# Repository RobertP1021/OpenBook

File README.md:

# OpenBook

## Diagrama

## Bill Of Materials

| Componenta | Datasheet | Model |
|------------|-----------|-------|
| ESP32-C6-WROOM-1-N8 | [Datasheet](https://www.espressif.com/sites/default/files/documentation/esp32-c6_datasheet_en.pdf) | [Model](https://www.snapeda.com/parts/ESP32-C6-WROOM-1-N8/Espressif+Systems/view-part/?ref=eda) |
| W25Q512JVEIQ | [Datasheet](https://www.winbond.com/resource-files/W25Q512JV%20RevI%2005132020%20Plus.pdf) | [Model](https://www.snapeda.com/parts/W25Q512JVEIQ/Winbond+Electronics/view-part/?ref=eda) |
| DS3231SN# | [Datasheet](https://datasheets.maximintegrated.com/en/ds/DS3231.pdf) | [Model](https://www.snapeda.com/parts/DS3231SN%23/Analog+Devices/view-part/?ref=eda) |
| MAX17048G+T10 | [Datasheet](https://datasheets.maximintegrated.com/en/ds/MAX17048-MAX17049.pdf) | [Model](https://www.snapeda.com/parts/MAX17048G+T10/Analog+Devices/view-part/?ref=eda) |
| BME688 | [Datasheet](https://www.bosch-sensortec.com/media/boschsensortec/downloads/datasheets/bst-bme688-ds000.pdf) | [Model](https://www.snapeda.com/parts/BME680/Bosch/view-part/?welcome=home) |
| MCP73831 | [Datasheet](https://ww1.microchip.com/downloads/en/DeviceDoc/20001984g.pdf) | [Model](https://www.snapeda.com/parts/MCP73831T-2ACI-OT/Microchip/view-part/?ref=eda) |
| BD5229G-TR | [Datasheet](https://fscdn.rohm.com/en/products/databook/datasheet/ic/power/voltage_detector/bd52xxg-e.pdf) | [Model](https://componentsearchengine.com/part-view/BD5229G-TR/ROHM%20Semiconductor) |
| USBLC6-2SC6Y | [Datasheet](https://www.st.com/resource/en/datasheet/usblc6-2.pdf) | [Model](https://www.snapeda.com/parts/USBLC6-2SC6Y/STMicroelectronics/view-part/?ref=eda) |
| 112A-TAAR-R03 | [Datasheet](https://www.attend.com.tw/sites/default/files/2022-05/112A-TAAR-R03.pdf) | [Model](https://www.snapeda.com/parts/112A-TAAR-R03/ATTEND/view-part/?ref=eda) |
| FH34SRJ-24S-0.5SH | [Datasheet](https://www.hirose.com/product/document?clcode=CL0684-0832-7-99&productname=FH34SRJ-24S-0.5SH(99)&series=FH34&documenttype=Catalog&lang=en&documentid=D49681_en) | [Model](https://www.snapeda.com/parts/FH34SRJ-24S-0.5SH(99)/Hirose/view-part/?ref=eda) |
| DMG2305UX-7 | [Datasheet](https://www.diodes.com/assets/Datasheets/DMG2305UX.pdf) | [Model](https://www.snapeda.com/parts/DMG2305UX-7/Diodes%20Inc./view-part/?ref=eda) |
| SI1308EDL-T1-GE3 | [Datasheet](https://www.vishay.com/docs/68732/si1308edl.pdf) | [Model](https://www.snapeda.com/parts/SI1308EDL-T1-GE3/Vishay+Siliconix/view-part/?ref=snap) |
| MBR0530 | [Datasheet](https://www.onsemi.com/pdf/datasheet/mbr0520lt1-d.pdf) | [Model](https://www.snapeda.com/parts/MBR0530/Onsemi/view-part/?ref=eda) |
| PGB1010603MR | [Datasheet](https://www.littelfuse.com/media?resourcetype=datasheets&itemid=3d1e98b7-4d37-463c-9380-c56c83b11c3c&filename=littelfuse-pulseguard-pgb1) | [Model](https://www.snapeda.com/parts/PGB1010603MR/Littelfuse/view-part/?ref=eda) |
| XC6220A331MR-G | [Datasheet](https://www.torexsemi.com/file/xc6220/XC6220.pdf) | [Model](https://www.snapeda.com/parts/XC6220A331MR-G/Torex+Semiconductor/view-part/?ref=eda) |
| EVQPUJ02K | [Datasheet](https://industrial.panasonic.com/cdbs/www-data/pdf/ATV0000/ATV0000CE5.pdf) | [Model](https://www.snapeda.com/parts/EVQPUJ02K/Panasonic/view-part/?ref=eda) |
| GDEH0154D67 | [Datasheet](https://www.good-display.com/companyfile/203.html) | [Model](https://www.good-display.com/product/207.html) |
| CPH3225A | [Datasheet](https://www.sii.co.jp/en/quartz/files/2021/03/CPH3225A_E.pdf) | [Model](https://www.snapeda.com/parts/CPH3225A/Seiko+Instruments/view-part/?ref=eda) |

## Functionalitatea hardware

Proiectul foloseste un ESP32-C6 ca microcontroller central, cu urmatoarele componente principale:

1. **Display E-Ink (GDEH0154D67)** - afisaj de 1.54" cu 200x200 pixeli conectat prin SPI, perfect pentru afisarea datelor cu consum minim de energie, deoarece consuma curent doar la actualizarea ecranului.

2. **Memorie Flash externa (W25Q512JVEIQ)** - 64MB de stocare SPI pentru date, configuratii si loguri cand dispozitivul este in modul deep sleep.

3. **Senzor de mediu (BME688)** - masoara temperatura, umiditatea, presiunea atmosferica si calitatea aerului, conectat prin I2C.

4. **Ceas RTC (DS3231)** - mentine ora exacta chiar si cand dispozitivul este oprit, conectat prin I2C.

5. **Sistem de alimentare**: 
   - Baterie LiPo 3.7V
   - Circuit de incarcare (MCP73831)
   - Monitor baterie (MAX17048G)
   - Regulator LDO 3.3V (XC6220A331MR-G)
   - Convertor 5V (pentru componente care necesita 5V)

6. **Interfata USB-C** - pentru incarcare si comunicatii, cu protectie ESD (USBLC6-2SC6Y).

7. **Butoane tactile (EVQPUJ02K)** - 3 butoane pentru interfata utilizator.

8. **Slot card microSD** - pentru stocarea datelor in volum mare.

## Descrierea pinilor ESP32-C6

- **GPIO1-2**: Magistrala I2C principala pentru conectarea senzorilor si RTC-ului DS3231, fiind pinii hardware dedicati pentru I2C.

- **GPIO3**: Pin RESET pentru reinitializarea sistemului.

- **GPIO4**: SS_SD pentru selectarea cardului microSD, parte a interfetei SPI dedicate cardului.

- **GPIO5**: Pin EPD_DC pentru controlul displayului E-Ink (Data/Command).

- **GPIO6**: Pin SPI SCK (clock) utilizat pentru comunicatia cu displayul si alte dispozitive SPI.

- **GPIO7**: Pin MOSI pentru transferul de date spre dispozitivele SPI.

- **GPIO8-9**: Pini pentru interfata RTC (32kHz si INT_RTC), utilizati pentru wake-up si sincronizare.

- **GPIO10**: Pin pentru controlul FLASH_CS, selectand memoria flash externa.

- **GPIO11**: Pin EPD_CS pentru selectarea displayului E-Ink.

- **GPIO12**: Pin EPD_RST pentru resetarea displayului E-Ink.

- **GPIO13-14**: Pini USB_D- si USB_D+ pentru comunicatia USB.

- **GPIO15**: Pin IO/BOOT pentru controlul bootarii sistemului.

- **GPIO16-18**: Pini pentru controlul displayului e-ink (EPD_3V3, EPD_BUSY).

- **GPIO19-21**: Pini SCL, SDA pentru o secunda interfata I2C folosita pentru comunicatie cu senzorii adaugati.

- **GPIO22-23**: Pini pentru control I/O general si semnale de control pentru display.

- **GPIO26-28**: Pini pentru LED-uri de status si controlul modulului.

## Poze

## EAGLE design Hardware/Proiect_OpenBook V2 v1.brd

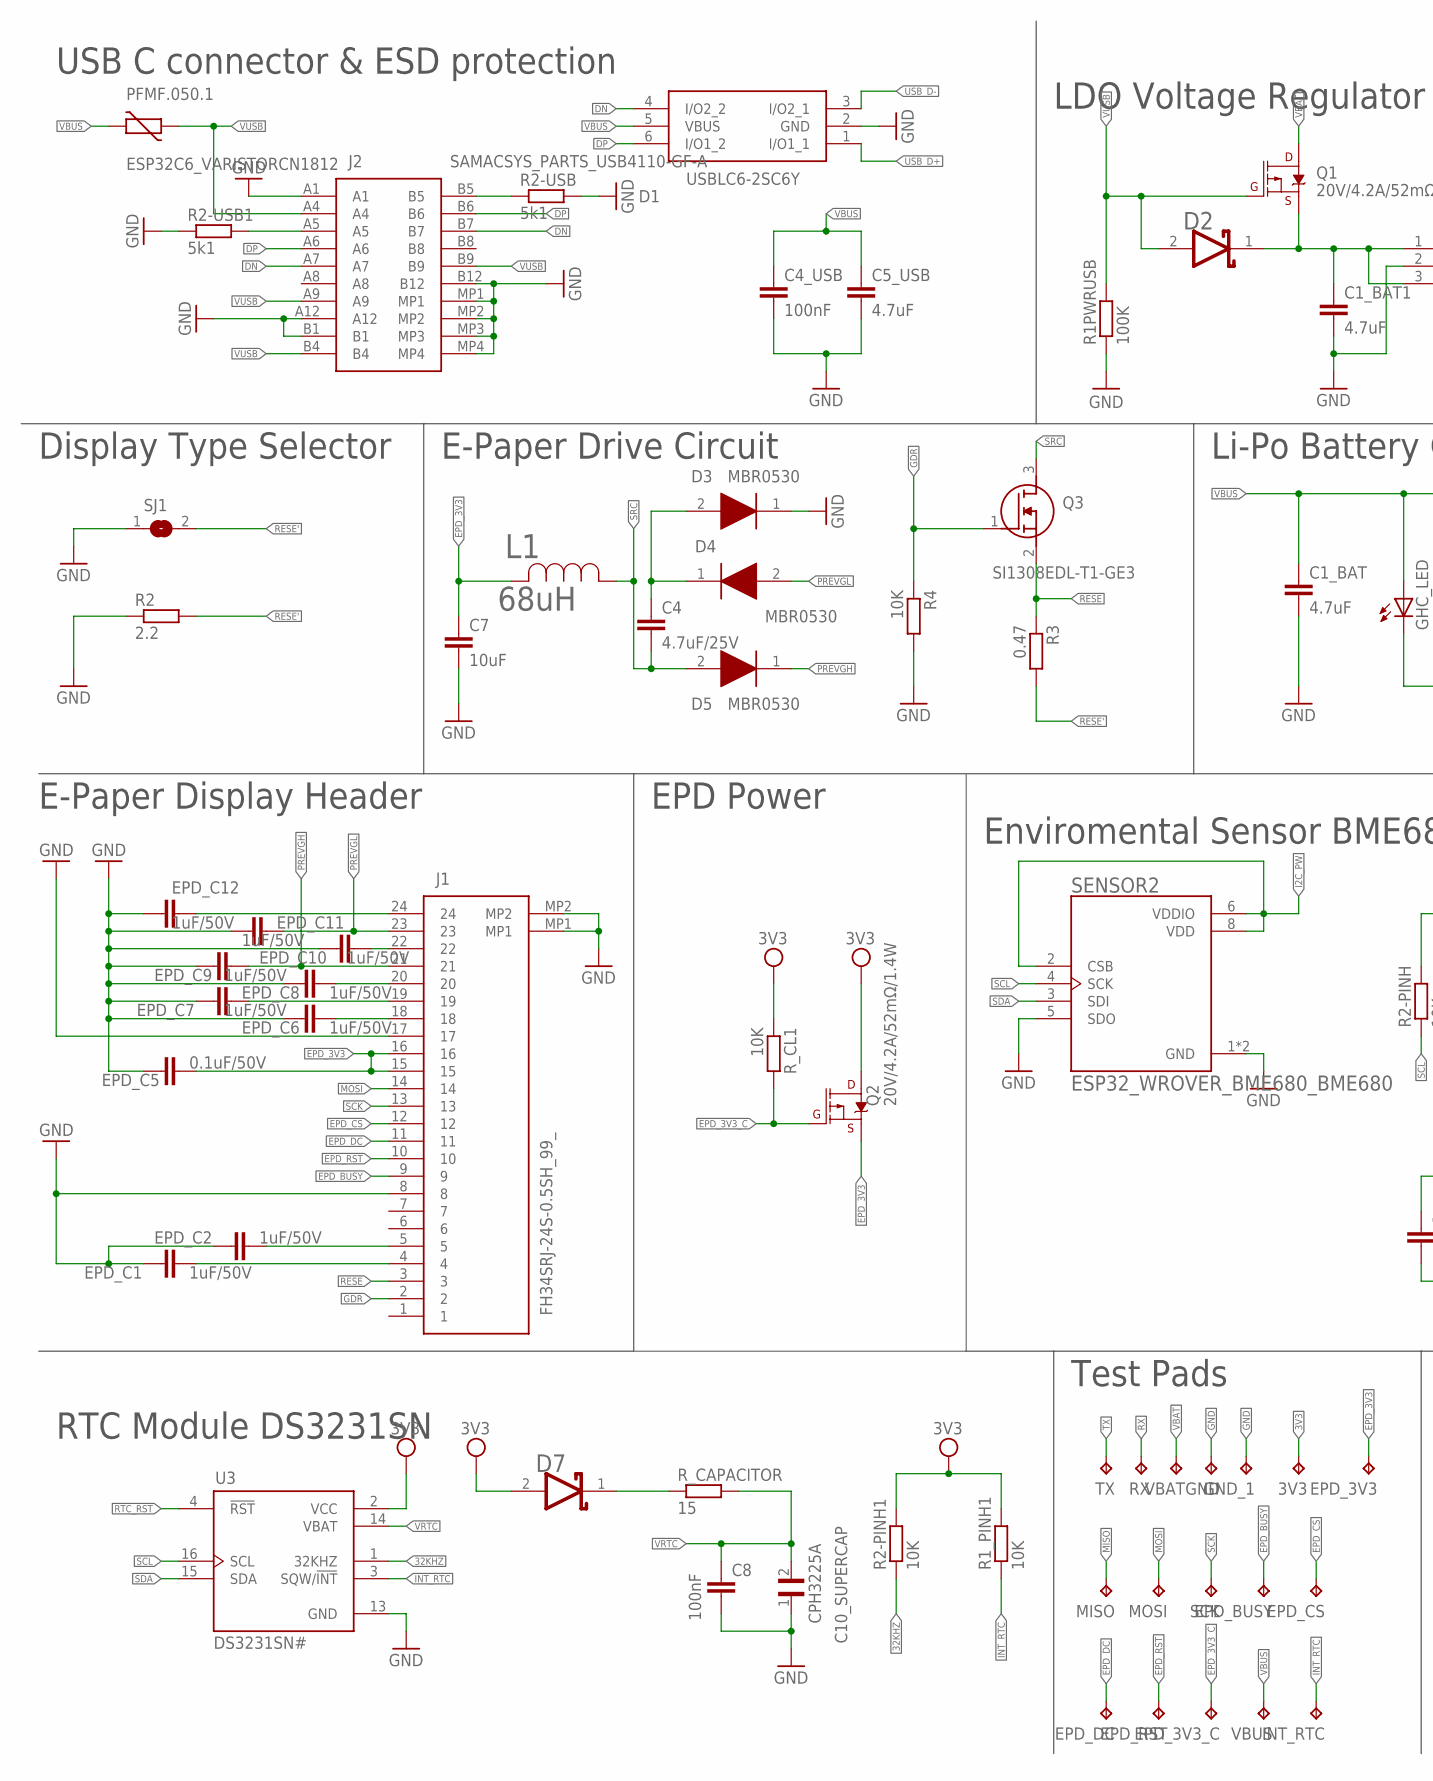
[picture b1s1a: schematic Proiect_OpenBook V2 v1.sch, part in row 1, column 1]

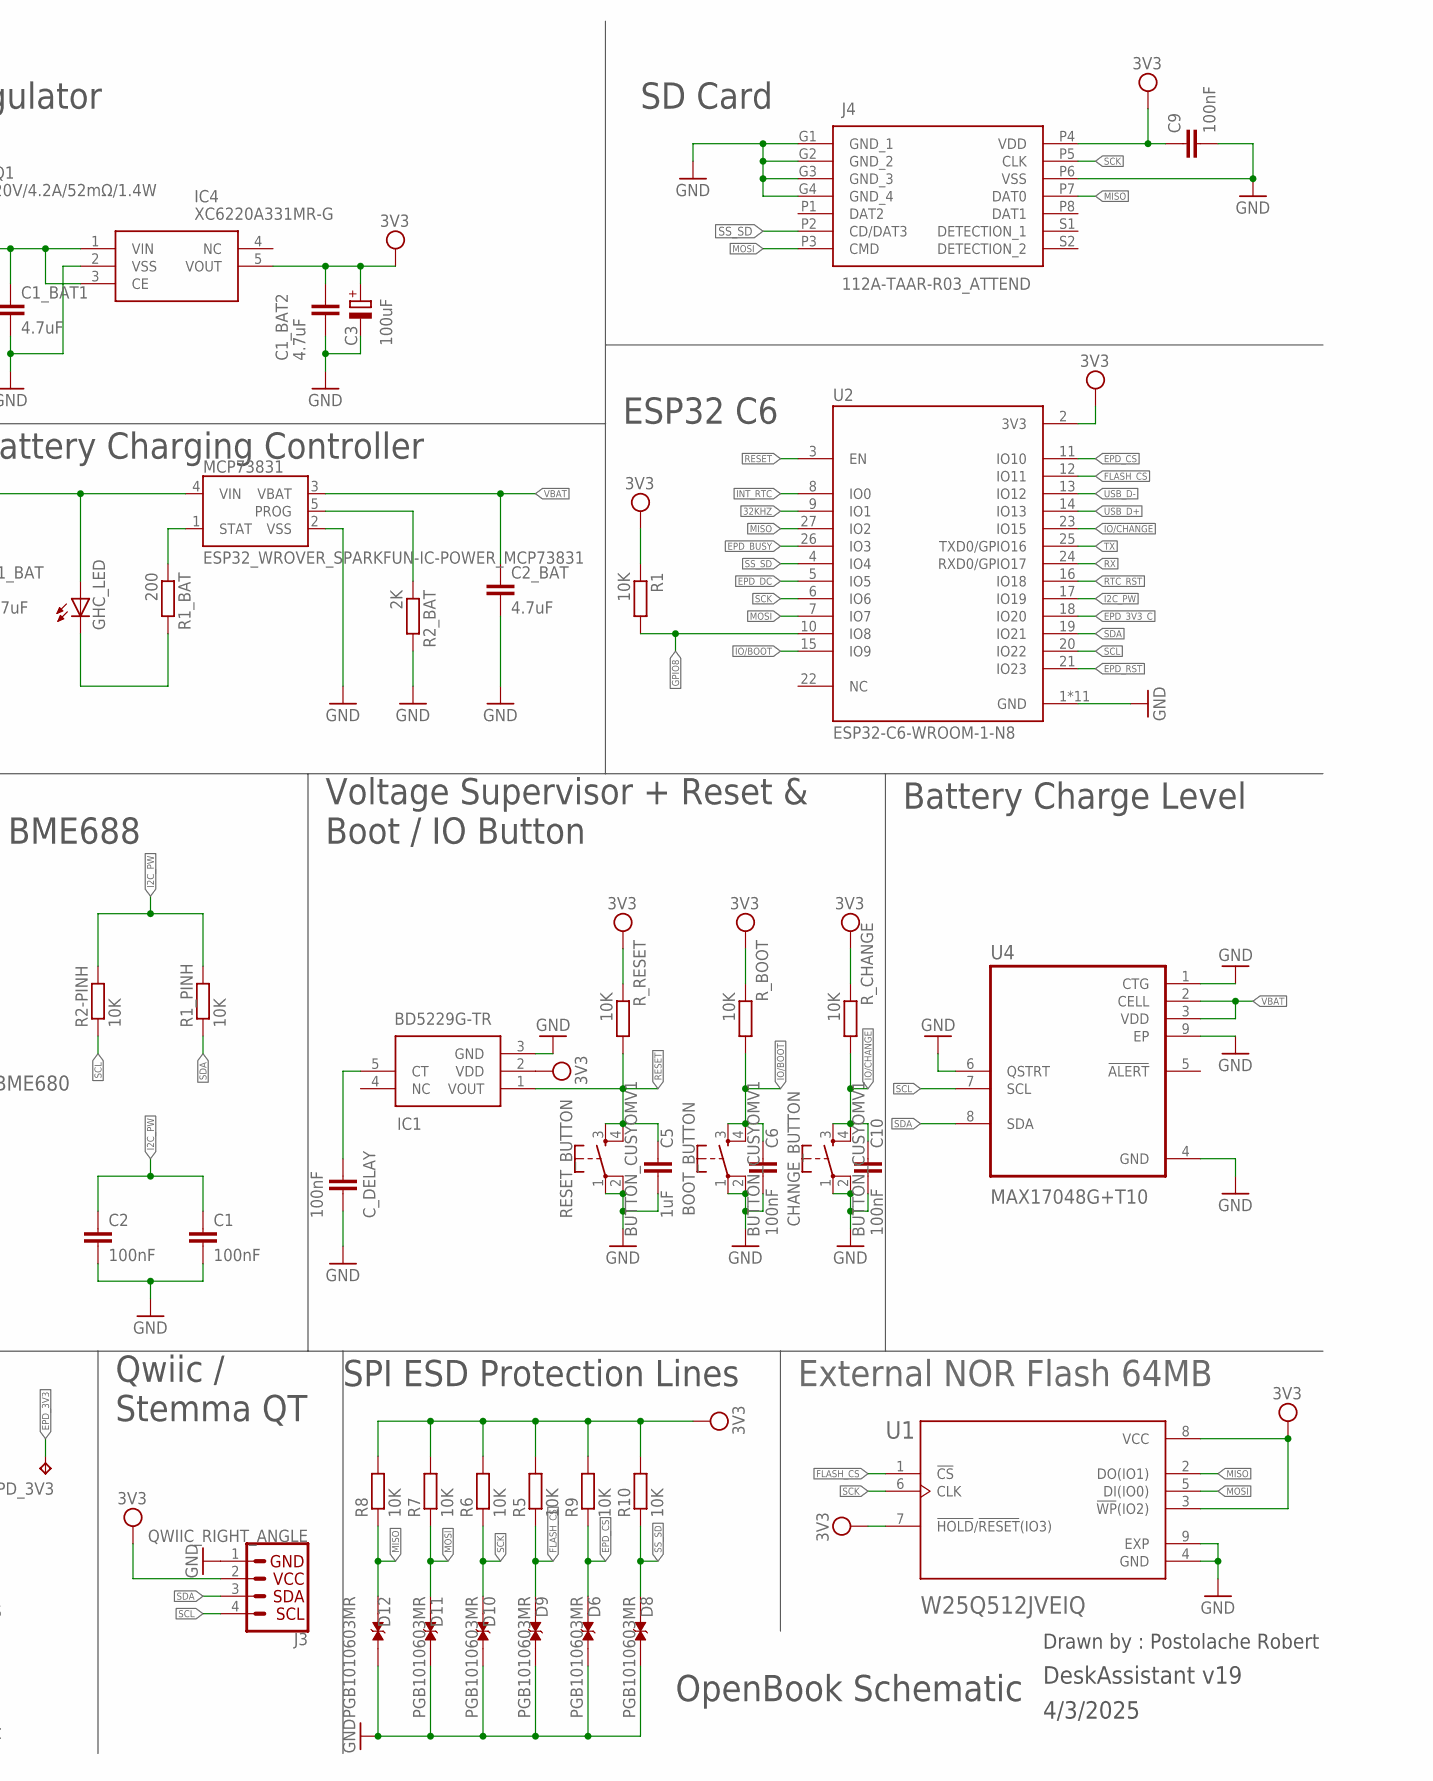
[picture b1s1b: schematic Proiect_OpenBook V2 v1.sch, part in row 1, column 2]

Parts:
3V3: TPTP20R; TP20R
BOOT_BUTTON: BUTTON_CUSYOMV1; MYBUTTON
C1, C2, C4_USB, C6, C8, C9, C10: 100nF; ESP32_WROVER_EAGLE-LTSPICE_C0402
C1_BAT, C1_BAT1, C1_BAT2, C2_BAT, C5_USB: 4.7uF; ESP32_WROVER_EAGLE-LTSPICE_C0402
C3: 100uF; RCL_CT3528
C4: 4.7uF/25V; ESP32_WROVER_EAGLE-LTSPICE_C0402
C5: 1uF; ESP32_WROVER_EAGLE-LTSPICE_C0402
C7: 10uF; ESP32_WROVER_EAGLE-LTSPICE_C0402
C10_SUPERCAP: CPH3225A; CAPCP3225X100N
CHANGE_BUTTON: BUTTON_CUSYOMV1; MYBUTTON
C_DELAY: 100nF; ESP32_WROVER_EAGLE-LTSPICE_C0402
D1: USBLC6-2SC6Y; SOT95P280X145-6N
D2, D7: ESP32_WROVER_AVX---SD0805S020S1R0_AVX_SD0805S020S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; ESP32_WROVER_AVX---SD0805S020S1R0_AVX_SD0805S020S1R0_0
D3, D4, D5: MBR0530; SOD3716X135N
D6, D8, D9, D10, D11, D12: PGB1010603MR; DIOC1608X36N
EPD_3V3, EPD_3V3_C: TPTP20R; TP20R
EPD_BUSY: TPTP20R; TP20R
EPD_C1, EPD_C2, EPD_C6, EPD_C7, EPD_C8, EPD_C9, EPD_C10, EPD_C11, EPD_C12: 1uF/50V; ESP32_WROVER_EAGLE-LTSPICE_C0402
EPD_C5: 0.1uF/50V; ESP32_WROVER_EAGLE-LTSPICE_C0402
EPD_CS: TPTP20R; TP20R
EPD_DC: TPTP20R; TP20R
EPD_RST: TPTP20R; TP20R
GHC_LED: ADAFRUIT_LEDCHIP-LED0603; ADAFRUIT_CHIP-LED0603
GND: TPTP20R; TP20R
GND_1: TPTP20R; TP20R
IC1: BD5229G-TR; SOT95P280X125-5N
IC4: XC6220A331MR-G; SOT95P280X120-5N
INT_RTC: TPTP20R; TP20R
J1: FH34SRJ-24S-0.5SH_99_; FH34SRJ24S05SH99
J2: SAMACSYS_PARTS_USB4110-GF-A; SAMACSYS_PARTS_USB4110GFA
J3: QWIIC_RIGHT_ANGLE; JST04_1MM_RA
J4: 112A-TAAR-R03_ATTEND; 112ATAARR03ATTEND
L1: 68uH; IND_4828-WE-TPC_WRE
MCP73831: ESP32_WROVER_SPARKFUN-IC-POWER_MCP73831; ESP32_WROVER_SPARKFUN-IC-POWER_SOT23-5
MISO: TPTP20R; TP20R
MOSI: TPTP20R; TP20R
PFMF.050.1: ESP32C6_VARISTORCN1812; ESP32C6_VARISTOR_CT/CN1812
Q1, Q2: 20V/4.2A/52mΩ/1.4W; ESP32_WROVER_SPARKFUN-DISCRETESEMI_SOT23-3
Q3: SI1308EDL-T1-GE3; SOT65P210X110-3N
R1, R1_PINH, R1_PINH1, R2-PINH, R2-PINH1, R4, R5, R6, R7, R8, R9, R10: 10K; ESP32_WROVER_EAGLE-LTSPICE_R0402
R1PWRUSB: 100K; ESP32_WROVER_EAGLE-LTSPICE_R0402
R1_BAT: 200; ESP32_WROVER_EAGLE-LTSPICE_R0402
R2: 2.2; ESP32_WROVER_EAGLE-LTSPICE_R0402
R2-USB, R2-USB1: 5k1; ESP32_WROVER_EAGLE-LTSPICE_R0402
R2_BAT: 2K; ESP32_WROVER_EAGLE-LTSPICE_R0402
R3: 0.47; ESP32_WROVER_EAGLE-LTSPICE_R0402
RESET_BUTTON: BUTTON_CUSYOMV1; MYBUTTON
RX: TPTP20R; TP20R
R_BOOT: 10K; ESP32_WROVER_EAGLE-LTSPICE_R0402
R_CAPACITOR: 15; ESP32_WROVER_EAGLE-LTSPICE_R0402
R_CHANGE: 10K; ESP32_WROVER_EAGLE-LTSPICE_R0402
R_CL1: 10K; ESP32_WROVER_EAGLE-LTSPICE_R0402
R_RESET: 10K; ESP32_WROVER_EAGLE-LTSPICE_R0402
SCK: TPTP20R; TP20R
SENSOR2: ESP32_WROVER_BME680_BME680; ESP32_WROVER_BME680_PSON80P300X300X100-8N
SJ1: SJ
TX: TPTP20R; TP20R
U1: W25Q512JVEIQ; SON127P600X800X80-9N
U2: ESP32-C6-WROOM-1-N8; XCVR_ESP32-C6-WROOM-1-N8
U3: DS3231SN#; SOIC127P1032X265-16N
U4: MAX17048G+T10; SON50P200X200X80-9N
VBAT: TPTP20R; TP20R
VBUS: TPTP20R; TP20R

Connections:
3V3: 3V3.TP, C1_BAT2.1, C3.+, C9.1, D7.2 (ANODE), IC1.2 (VDD), IC4.5 (VOUT), J3.2, J4.P4 (VDD), Q2.3 (D), R1.1, R1_PINH1.2, R2-PINH1.2, R5.2, R6.2, R7.2, R8.2, R9.2, R10.2, R_BOOT.1, R_CHANGE.1, R_CL1.1, R_RESET.1, U1.3 (!WP!(IO2)), U1.7 (!HOLD!/!RESET!(IO3)), U1.8 (VCC), U2.2 (3V3), U3.2 (VCC)
32KHZ: R2-PINH1.1, U2.9 (IO1), U3.1 (32KHZ)
DN: D1.4 (I/O2_2), J2.A7, J2.B7
DP: D1.6 (I/O1_2), J2.A6, J2.B6
EPD_3V3: C7.1, EPD_3V3.TP, EPD_C5.1, J1.15, J1.16, L1.2, Q2.2 (S)
EPD_3V3_C: EPD_3V3_C.TP, Q2.1 (G), R_CL1.2, U2.18 (IO20)
EPD_BUSY: EPD_BUSY.TP, J1.9, U2.26 (IO3)
EPD_CS: D6.1, EPD_CS.TP, J1.12, R9.1, U2.11 (IO10)
EPD_DC: EPD_DC.TP, J1.11, U2.5 (IO5)
EPD_RST: EPD_RST.TP, J1.10, U2.21 (IO23)
FLASH_CS: D9.1, R5.1, U1.1 (!CS), U2.12 (IO11)
GDR: J1.2, Q3.1 (G), R4.1
GND: BOOT_BUTTON.1, BOOT_BUTTON.2, C1.2, C1_BAT.2, C1_BAT1.2, C1_BAT2.2, C2.2, C2_BAT.2, C3.-, C4_USB.2, C5.2, C5_USB.2, C6.2, C7.2, C8.2, C9.2, C10.2, C10_SUPERCAP.1, CHANGE_BUTTON.1, CHANGE_BUTTON.2, C_DELAY.2, D1.2 (GND), D3.1 (K), D6.2, D8.2, D9.2, D10.2, D11.2, D12.2, EPD_C1.2, EPD_C2.2, EPD_C5.2, EPD_C6.2, EPD_C7.2, EPD_C8.2, EPD_C9.2, EPD_C10.2, EPD_C11.2, EPD_C12.2, GND.TP, GND_1.TP, IC1.3 (GND), IC4.2 (VSS), J1.8, J1.17, J1.MP1, J1.MP2, J2.A1, J2.A12, J2.B1, J2.B12, J2.MP1, J2.MP2, J2.MP3, J2.MP4, J3.1, J4.G1 (GND_1), J4.G2 (GND_2), J4.G3 (GND_3), J4.G4 (GND_4), J4.P6 (VSS), MCP73831.2 (VSS), R1PWRUSB.1, R2.1, R2-USB.2, R2-USB1.1, R2_BAT.2, R4.2, RESET_BUTTON.1, RESET_BUTTON.2, SENSOR2.1 (GND), SENSOR2.5 (SDO), SENSOR2.7 (GND), SJ1.1, U1.4 (GND), U1.9 (EXP), U2.1 (GND), U2.28 (GND), U2.29_1 (GND), U2.29_2 (GND), U2.29_3 (GND), U2.29_4 (GND), U2.29_5 (GND), U2.29_6 (GND), U2.29_7 (GND), U2.29_8 (GND), U2.29_9 (GND), U3.13 (GND), U4.1 (CTG), U4.4 (GND), U4.6 (QSTRT), U4.9 (EP)
GPIO8: R1.2, U2.10 (IO8)
I2C_PW: C1.1, C2.1, R1_PINH.2, R2-PINH.2, SENSOR2.2 (CSB), SENSOR2.6 (VDDIO), SENSOR2.8 (VDD), U2.17 (IO19)
INT_RTC: INT_RTC.TP, R1_PINH1.1, U2.8 (IO0), U3.3 (SQW/!INT)
IO/BOOT: BOOT_BUTTON.3, BOOT_BUTTON.4, C6.1, R_BOOT.2, U2.15 (IO9)
IO/CHANGE: C10.1, CHANGE_BUTTON.3, CHANGE_BUTTON.4, R_CHANGE.2, U2.23 (IO15)
MISO: D12.1, J4.P7 (DAT0), MISO.TP, R8.1, U1.2 (DO(IO1)), U2.27 (IO2)
MOSI: D11.1, J1.14, J4.P3 (CMD), MOSI.TP, R7.1, U1.5 (DI(IO0)), U2.7 (IO7)
unnamed: J2.B5, R2-USB.1
unnamed: J2.A5, R2-USB1.2
unnamed: C1_BAT1.1, D2.1 (CATHODE), IC4.1 (VIN), IC4.3 (CE), Q1.2 (S)
unnamed: EPD_C12.1, J1.24
unnamed: GHC_LED.C, R1_BAT.2
unnamed: C4.1, D3.2 (A), D4.1 (K)
unnamed: MCP73831.1 (STAT), R1_BAT.1
unnamed: MCP73831.5 (PROG), R2_BAT.1
unnamed: C_DELAY.1, IC1.5 (CT)
unnamed: EPD_C10.1, J1.22
unnamed: EPD_C8.1, J1.20
unnamed: EPD_C7.1, J1.19
unnamed: EPD_C6.1, J1.18
unnamed: EPD_C1.1, J1.4
unnamed: EPD_C2.1, J1.5
unnamed: D7.1 (CATHODE), R_CAPACITOR.1
PREVGH: D5.1 (K), EPD_C9.1, J1.21
PREVGL: D4.2 (A), EPD_C11.1, J1.23
RESE: J1.3, Q3.2 (S), R3.1
RESE': R2.2, R3.2, SJ1.2
RESET: C5.1, IC1.1 (VOUT), RESET_BUTTON.3, RESET_BUTTON.4, R_RESET.2, U2.3 (EN)
RTC_RST: U2.16 (IO18), U3.4 (!RST)
RX: RX.TP, U2.24 (RXD0/GPIO17)
SCK: D10.1, J1.13, J4.P5 (CLK), R6.1, SCK.TP, U1.6 (CLK), U2.6 (IO6)
SCL: J3.4, R2-PINH.1, SENSOR2.4 (SCK), U2.20 (IO22), U3.16 (SCL), U4.7 (SCL)
SDA: J3.3, R1_PINH.1, SENSOR2.3 (SDI), U2.19 (IO21), U3.15 (SDA), U4.8 (SDA)
SRC: C4.2, D5.2 (A), L1.1, Q3.3 (D)
SS_SD: D8.1, J4.P2 (CD/DAT3), R10.1, U2.4 (IO4)
TX: TX.TP, U2.25 (TXD0/GPIO16)
USB_D+: D1.1 (I/O1_1), U2.14 (IO13)
USB_D-: D1.3 (I/O2_1), U2.13 (IO12)
VBAT: C2_BAT.1, MCP73831.3 (VBAT), Q1.3 (D), U4.2 (CELL), U4.3 (VDD), VBAT.TP
VBUS: C1_BAT.1, C4_USB.1, C5_USB.1, D1.5 (VBUS), GHC_LED.A, MCP73831.4 (VIN), PFMF.050.1.2, VBUS.TP
VRTC: C8.1, C10_SUPERCAP.2, R_CAPACITOR.2, U3.14 (VBAT)
VUSB: D2.2 (ANODE), J2.A4, J2.A9, J2.B4, J2.B9, PFMF.050.1.1, Q1.1 (G), R1PWRUSB.2

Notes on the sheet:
USB C connector & ESD protection
LDO Voltage Regulator
SD Card
Display Type Selector
E-Paper Drive Circuit
Li-Po Battery Charging Controller
ESP32 C6
E-Paper Display Header
EPD Power
Enviromental Sensor BME688
Battery Charge Level
Voltage Supervisor + Reset & Boot / IO Button
Test Pads
Qwiic / Stemma QT
SPI ESD Protection Lines
External NOR Flash 64MB
RTC Module DS3231SN
Drawn by : Postolache Robert
4/3/2025
DeskAssistant v19
OpenBook Schematic

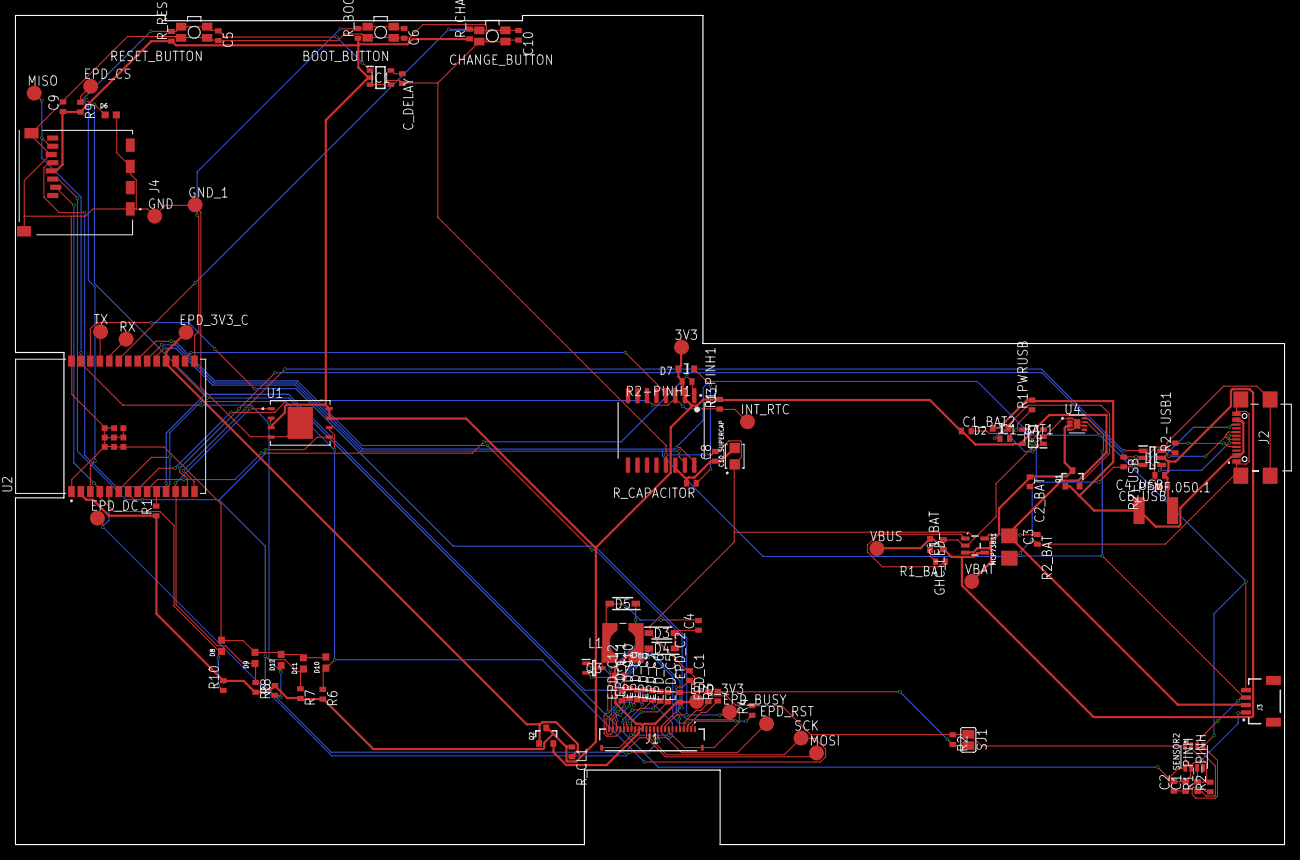
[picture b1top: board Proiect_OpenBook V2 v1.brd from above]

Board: 2 copper layers, 170.2 x 111.2 mm, 103 parts (0 on the bottom side), 55 nets.

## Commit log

2025-04-06 Create aaa
2025-04-06 schematic + pcb
2025-04-06 Create aa
2025-04-06 Create LICENSE
2025-04-14 Add files via upload
    Final

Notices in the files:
parts and their libraries:
COPYRIGHT: Copyright (C) 2024 Ultra Librarian. All rights reserved.
